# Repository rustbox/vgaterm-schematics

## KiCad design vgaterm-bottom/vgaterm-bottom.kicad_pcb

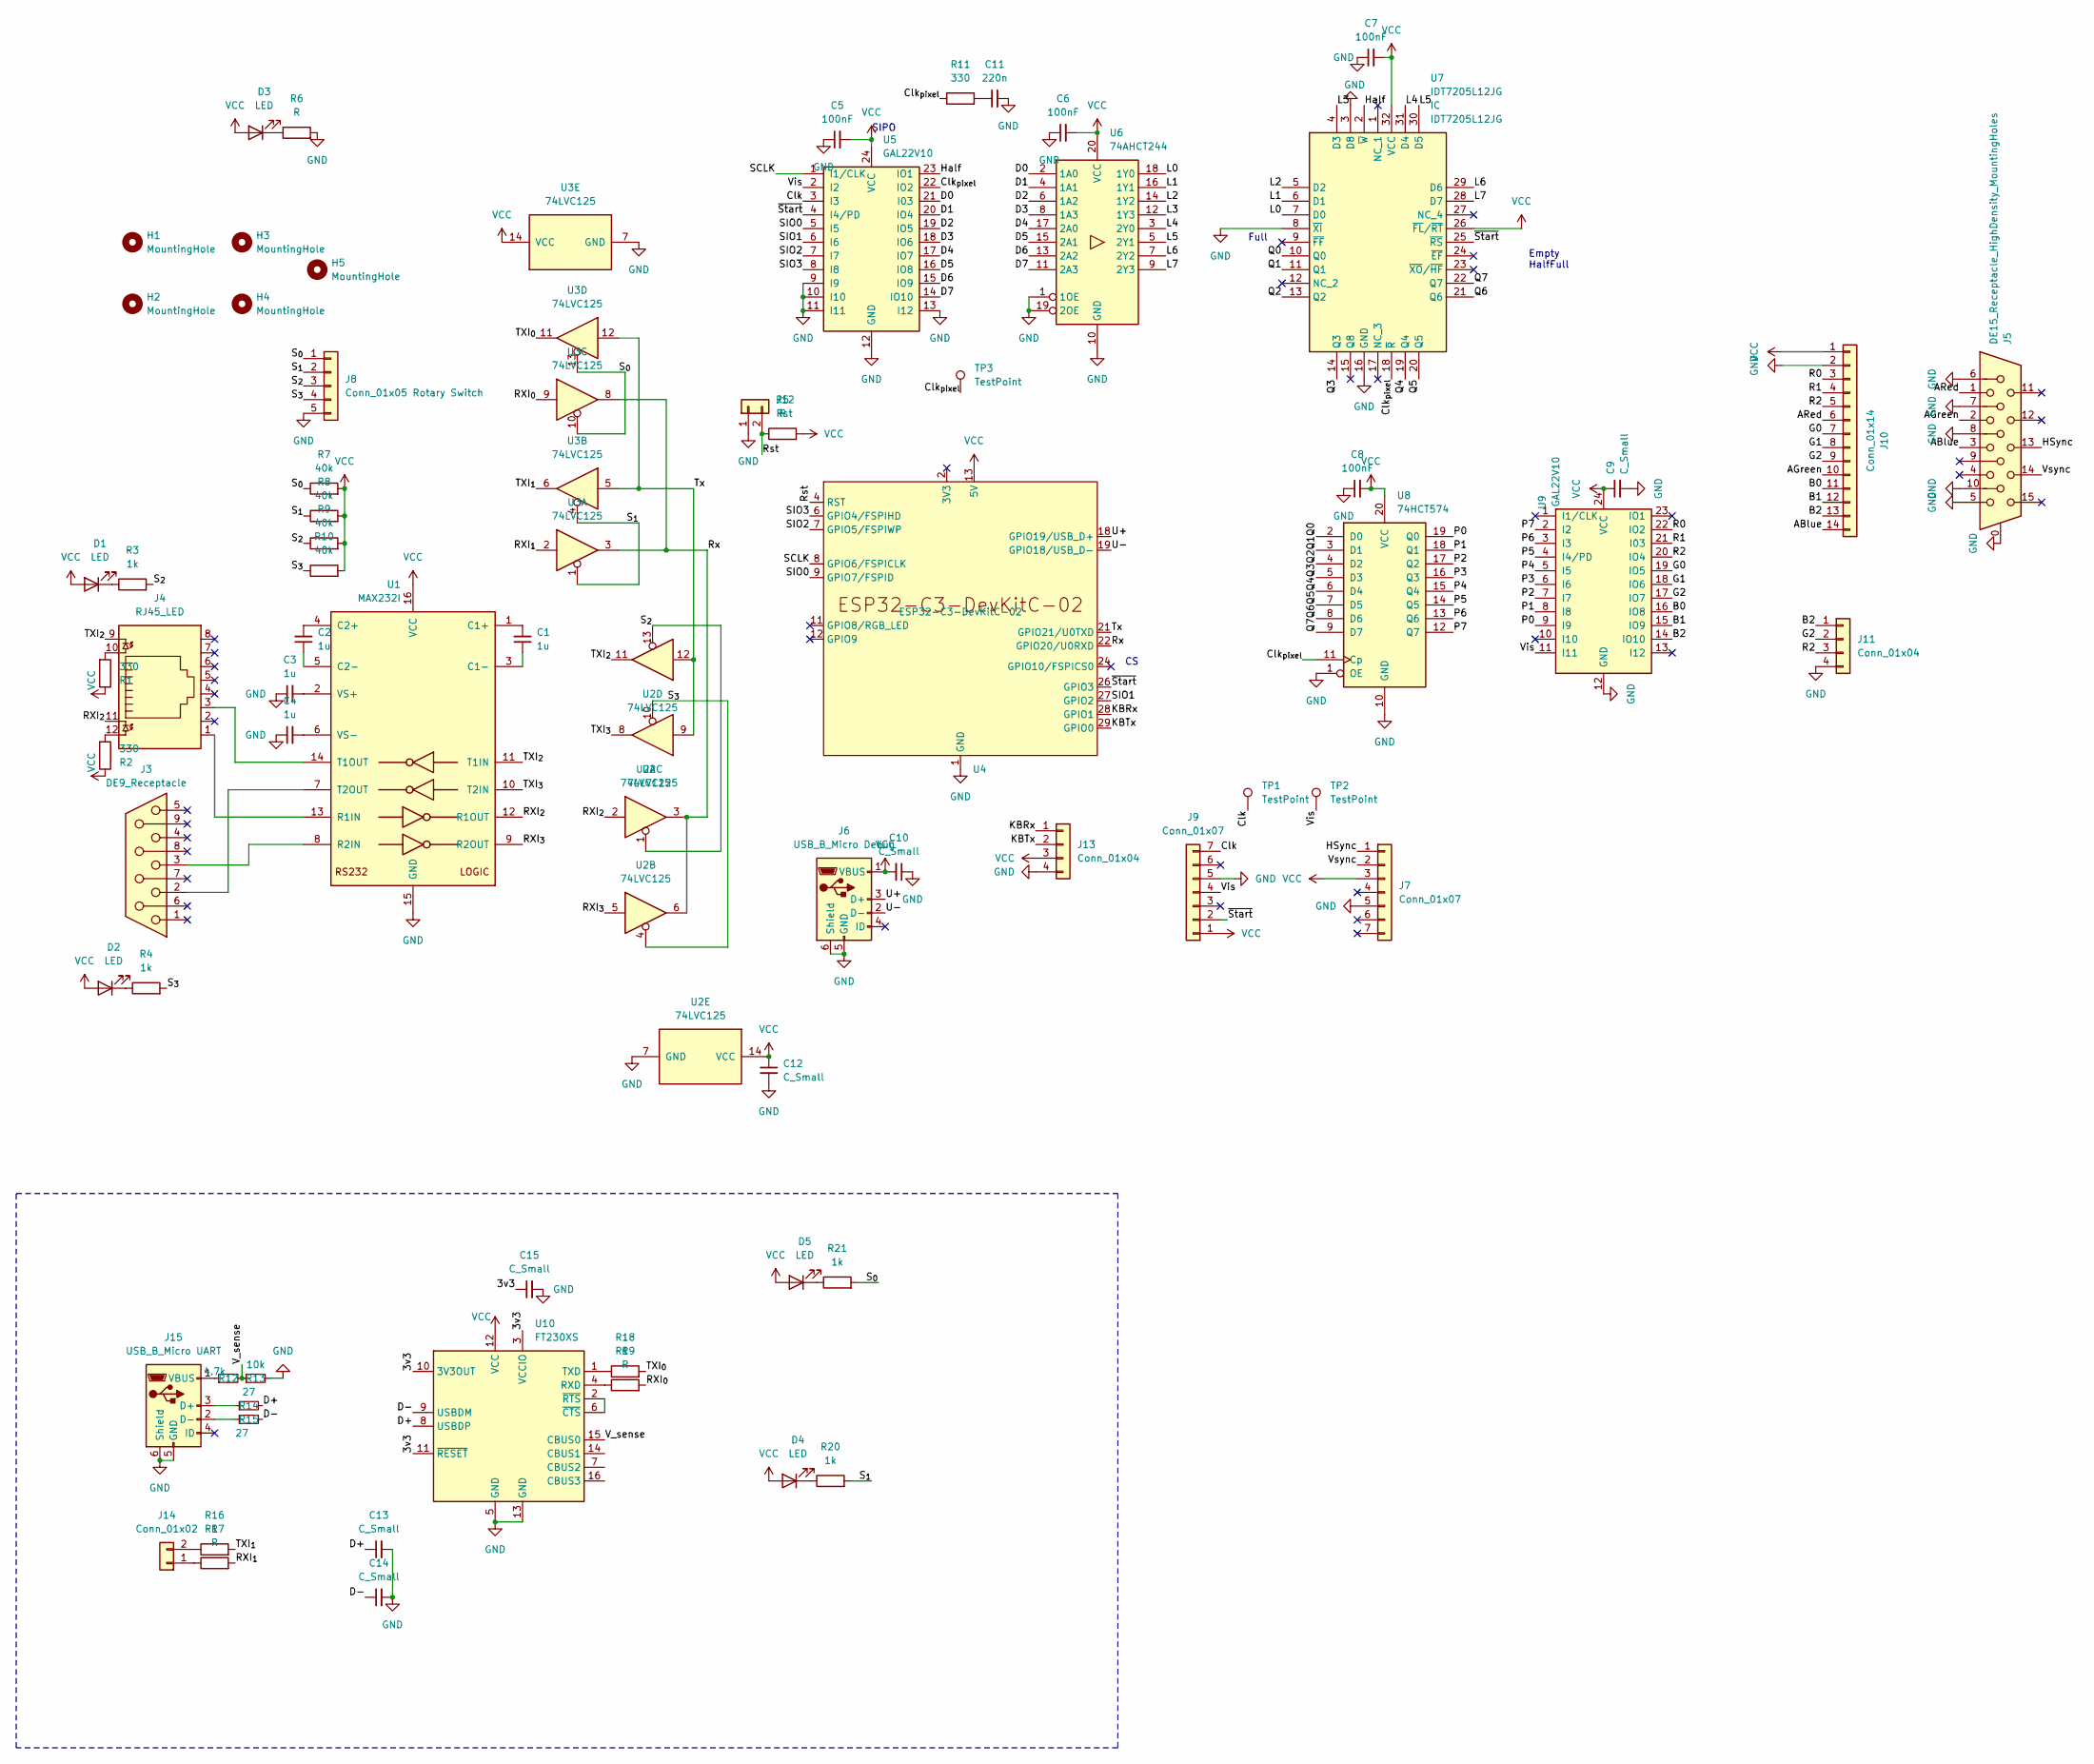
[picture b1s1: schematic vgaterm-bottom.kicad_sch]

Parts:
C1, C2, C3, C4: 1u; C_0805_2012Metric_Pad1.18x1.45mm_HandSolder
C5, C6, C7, C8: 100nF; C_0805_2012Metric_Pad1.18x1.45mm_HandSolder
C9, C10, C12, C13, C14, C15: C_Small; C_0805_2012Metric_Pad1.18x1.45mm_HandSolder
C11: 220n; C_0805_2012Metric_Pad1.18x1.45mm_HandSolder
D1, D2, D4, D5: LED; LED_D1.8mm_W1.8mm_H2.4mm_Horizontal_O1.27mm_Z1.6mm
D3: LED; LED_0805_2012Metric_Pad1.15x1.40mm_HandSolder
H1, H2, H3, H4, H5: MountingHole; MountingHole_2.2mm_M2_ISO7380
J3: DE9_Receptacle; DSUB-9_Female_Horizontal_P2.77x2.84mm_EdgePinOffset4.94mm_H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
J4: RJ45_LED; RJ45_Amphenol_RJHSE538X
J5: DE15_Receptacle_HighDensity_MountingHoles; DSUB-15-HD_Female_Horizontal_P2.29x2.54mm_EdgePinOffset8.35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
J6: USB_B_Micro Debug; USB_Micro-B_Molex-105017-0001
J7, J9: Conn_01x07; PinSocket_1x07_P2.54mm_Vertical
J8: Conn_01x05 Rotary Switch; PinHeader_1x05_P2.54mm_Vertical
J10: Conn_01x14; PinSocket_1x14_P2.54mm_Vertical
J11, J13: Conn_01x04; Molex_PicoBlade_53261-0471_1x04-1MP_P1.25mm_Horizontal
J12: Rst; PinHeader_1x02_P2.54mm_Vertical
J14: Conn_01x02; PinHeader_1x02_P2.54mm_Horizontal
J15: USB_B_Micro UART; USB_Micro-B_Molex-105017-0001
R1, R2, R11: 330; R_0805_2012Metric_Pad1.20x1.40mm_HandSolder
R3, R4, R20, R21: 1k; R_0805_2012Metric_Pad1.20x1.40mm_HandSolder
R5, R6, R16, R17, R18, R19: R; R_0805_2012Metric_Pad1.20x1.40mm_HandSolder
R7, R8, R9, R10: 40k; R_0805_2012Metric_Pad1.20x1.40mm_HandSolder
R12: 4.7k; R_0805_2012Metric_Pad1.20x1.40mm_HandSolder
R13: 10k; R_0805_2012Metric_Pad1.20x1.40mm_HandSolder
R14, R15: 27; R_0805_2012Metric_Pad1.20x1.40mm_HandSolder
TP1, TP2, TP3: TestPoint; TestPoint_THTPad_1.5x1.5mm_Drill0.7mm
U1: MAX232I; SOIC-16_3.9x9.9mm_P1.27mm
U2, U3: 74LVC125; TSSOP-14_4.4x5mm_P0.65mm
U4: ESP32-C3-DevKitC-02; espressif-2x15-devkit
U5, U9: GAL22V10; DIP-24_W7.62mm_Socket
U6: 74AHCT244; TSSOP-20_4.4x6.5mm_P0.65mm
U7: IDT7205L12JG; plcc32-socket; Manufacturer_Part_Number IDT7205L12JG
U8: 74HCT574; SOIC-20W_7.5x12.8mm_P1.27mm
U10: FT230XS; SSOP-16_3.9x4.9mm_P0.635mm

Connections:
3V3: U4.2 (3V3), U4.3 (3V3)
/3v3: C15.1, U10.3 (VCCIO), U10.10 (3V3OUT), U10.11 (~RESET)
/ABlue: J5.3, J10.14
/AGreen: J5.2, J10.10
/ARed: J5.1, J10.6
/B0: J10.11, U9.16 (IO8)
/B1: J10.12, U9.15 (IO9)
/B2: J10.13, J11.1, U9.14 (IO10)
/Clk: J9.7, TP1.1, U5.3 (I3)
/Clk_{pixel}: R11.1, TP3.1, U5.22 (IO2), U7.18 (~R), U8.11 (Cp)
/D0: U5.21 (I03), U6.2 (1A0)
/D1: U5.20 (IO4), U6.4 (1A1)
/D2: U5.19 (IO5), U6.6 (1A2)
/D3: U5.18 (IO6), U6.8 (1A3)
/D4: U5.17 (IO7), U6.17 (2A0)
/D5: U5.16 (IO8), U6.15 (2A1)
/D6: U5.15 (IO9), U6.13 (2A2)
/D7: U5.14 (IO10), U6.11 (2A3)
/D+: C13.1, R14.2, U10.8 (USBDP)
/D-: C14.1, R15.2, U10.9 (USBDM)
/G0: J10.7, U9.19 (IO5)
/G1: J10.8, U9.18 (IO6)
/G2: J10.9, J11.2, U9.17 (IO7)
/HSync: J5.13, J7.1
/Half: U5.23 (IO1), U7.2 (~W)
/KBRx: J13.1, U4.28 (GPIO1)
/KBTx: J13.2, U4.29 (GPIO0)
/L0: U6.18 (1Y0), U7.7 (D0)
/L1: U6.16 (1Y1), U7.6 (D1)
/L2: U6.14 (1Y2), U7.5 (D2)
/L3: U6.12 (1Y3), U7.4 (D3)
/L4: U6.3 (2Y0), U7.31 (D4)
/L5: U6.5 (2Y1), U7.30 (D5)
/L6: U6.7 (2Y2), U7.29 (D6)
/L7: U6.9 (2Y3), U7.28 (D7)
/P0: U8.19 (Q0), U9.9 (I9)
/P1: U8.18 (Q1), U9.8 (I8)
/P2: U8.17 (Q2), U9.7 (I7)
/P3: U8.16 (Q3), U9.6 (I6)
/P4: U8.15 (Q4), U9.5 (I5)
/P5: U8.14 (Q5), U9.4 (I4/PD)
/P6: U8.13 (Q6), U9.3 (I3)
/P7: U8.12 (Q7), U9.2 (I2)
/Q0: U7.10 (Q0), U8.2 (D0)
/Q1: U7.11 (Q1), U8.3 (D1)
/Q2: U7.13 (Q2), U8.4 (D2)
/Q3: U7.14 (Q3), U8.5 (D3)
/Q4: U7.19 (Q4), U8.6 (D4)
/Q5: U7.20 (Q5), U8.7 (D5)
/Q6: U7.21 (Q6), U8.8 (D6)
/Q7: U7.22 (Q7), U8.9 (D7)
/R0: J10.3, U9.22 (IO2)
/R1: J10.4, U9.21 (I03)
/R2: J10.5, J11.3, U9.20 (IO4)
/RXI_{0}: R19.2, U3.9
/RXI_{1}: R17.2, U3.2
/RXI_{2}: J4.11, U1.12 (R1OUT), U2.2
/RXI_{3}: U1.9 (R2OUT), U2.5
/Rst: J12.2, R5.1, U4.4 (RST)
/Rx: U2.3, U2.6, U3.3, U3.8, U4.22 (GPIO20/U0RXD)
/SCLK: U4.8 (GPIO6/FSPICLK), U5.1 (I1/CLK)
/SIO0: U4.9 (GPIO7/FSPID), U5.5 (I5)
/SIO1: U4.27 (GPIO2), U5.6 (I6)
/SIO2: U4.7 (GPIO5/FSPIWP), U5.7 (I7)
/SIO3: U4.6 (GPIO4/FSPIHD), U5.8 (I8)
/S_{0}: J8.1, R7.1, R21.2, U3.10, U3.13
/S_{1}: J8.2, R8.1, R20.2, U3.1, U3.4
/S_{2}: J8.3, R3.2, R9.1, U2.1, U2.13
/S_{3}: J8.4, R4.2, R10.1, U2.4, U2.10
/TXI_{0}: R18.2, U3.11
/TXI_{1}: R16.2, U3.6
/TXI_{2}: J4.9, U1.11 (T1IN), U2.11
/TXI_{3}: U1.10 (T2IN), U2.8
/Tx: U2.9, U2.12, U3.5, U3.12, U4.21 (GPIO21/U0TXD)
/U+: J6.3 (D+), U4.18 (GPIO19/USB_D+)
/U-: J6.2 (D-), U4.19 (GPIO18/USB_D-)
/V_sense: R12.2, R13.1, U10.15 (CBUS0)
/Vis: J9.4, TP2.1, U5.2 (I2), U9.11 (I11)
/Vsync: J5.14, J7.2
/~Start: J9.2, U4.26 (GPIO3), U5.4 (I4/PD), U7.25 (~RS)
GND: C3.1, C4.1, C5.1, C6.1, C7.1, C8.1, C9.2, C10.1, C11.2, C12.2, C13.2, C14.2, C15.2, J5.0, J5.5, J5.6, J5.7, J5.8, J5.10, J6.5 (GND), J6.6 (Shield), J7.5, J8.5, J9.5, J10.2, J11.4, J12.1, J13.4, J15.5 (GND), J15.6 (Shield), R6.2, R13.2, U1.15 (GND), U2.7 (GND), U3.7 (GND), U4.1 (GND), U4.5 (GND), U4.10 (GND), U4.15 (GND), U4.16 (GND), U4.17 (GND), U4.20 (GND), U4.23 (GND), U4.25 (GND), U4.30 (GND), U5.9 (I9), U5.10 (I10), U5.11 (I11), U5.12 (GND), U5.13 (I12), U6.1 (1OE), U6.10 (GND), U6.19 (2OE), U7.3 (D8), U7.8 (~XI), U7.16 (GND), U8.1 (OE), U8.10 (GND), U9.12 (GND), U10.5 (GND), U10.13 (GND)
unnamed: C11.1, R11.2
unnamed: D1.1 (K), R3.1
unnamed: D2.1 (K), R4.1
unnamed: D3.1 (K), R6.1
unnamed: D4.1 (K), R20.1
unnamed: D5.1 (K), R21.1
unnamed: J4.10, R1.2
unnamed: J4.12, R2.2
unnamed: J14.1, R17.1
unnamed: J14.2, R16.1
unnamed: J15.3 (D+), R14.1
unnamed: J15.2 (D-), R15.1
unnamed: J15.1 (VBUS), R12.1
unnamed: C1.2, U1.1 (C1+)
unnamed: C1.1, U1.3 (C1-)
unnamed: C2.2, U1.4 (C2+)
unnamed: C2.1, U1.5 (C2-)
unnamed: J4.1, U1.13 (R1IN)
unnamed: J3.3, U1.8 (R2IN)
unnamed: J4.3, U1.14 (T1OUT)
unnamed: J3.2, U1.7 (T2OUT)
unnamed: C3.2, U1.2 (VS+)
unnamed: C4.2, U1.6 (VS-)
unnamed: R19.1, U10.4 (RXD)
unnamed: R18.1, U10.1 (TXD)
unnamed: U10.2 (~RTS), U10.6 (~CTS)
VCC: C5.2, C6.2, C7.2, C8.2, C9.1, C10.2, C12.1, D1.2 (A), D2.2 (A), D3.2 (A), D4.2 (A), D5.2 (A), J6.1 (VBUS), J7.3, J9.1, J10.1, J13.3, R1.1, R2.1, R5.2, R7.2, R8.2, R9.2, R10.2, U1.16 (VCC), U2.14 (VCC), U3.14 (VCC), U4.13 (5V), U4.14 (5V), U5.24 (VCC), U6.20 (VCC), U7.26 (~FL/~RT), U7.32 (VCC), U8.20 (VCC), U9.24 (VCC), U10.12 (VCC)

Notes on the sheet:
Empty HalfFull
SIPO
Full

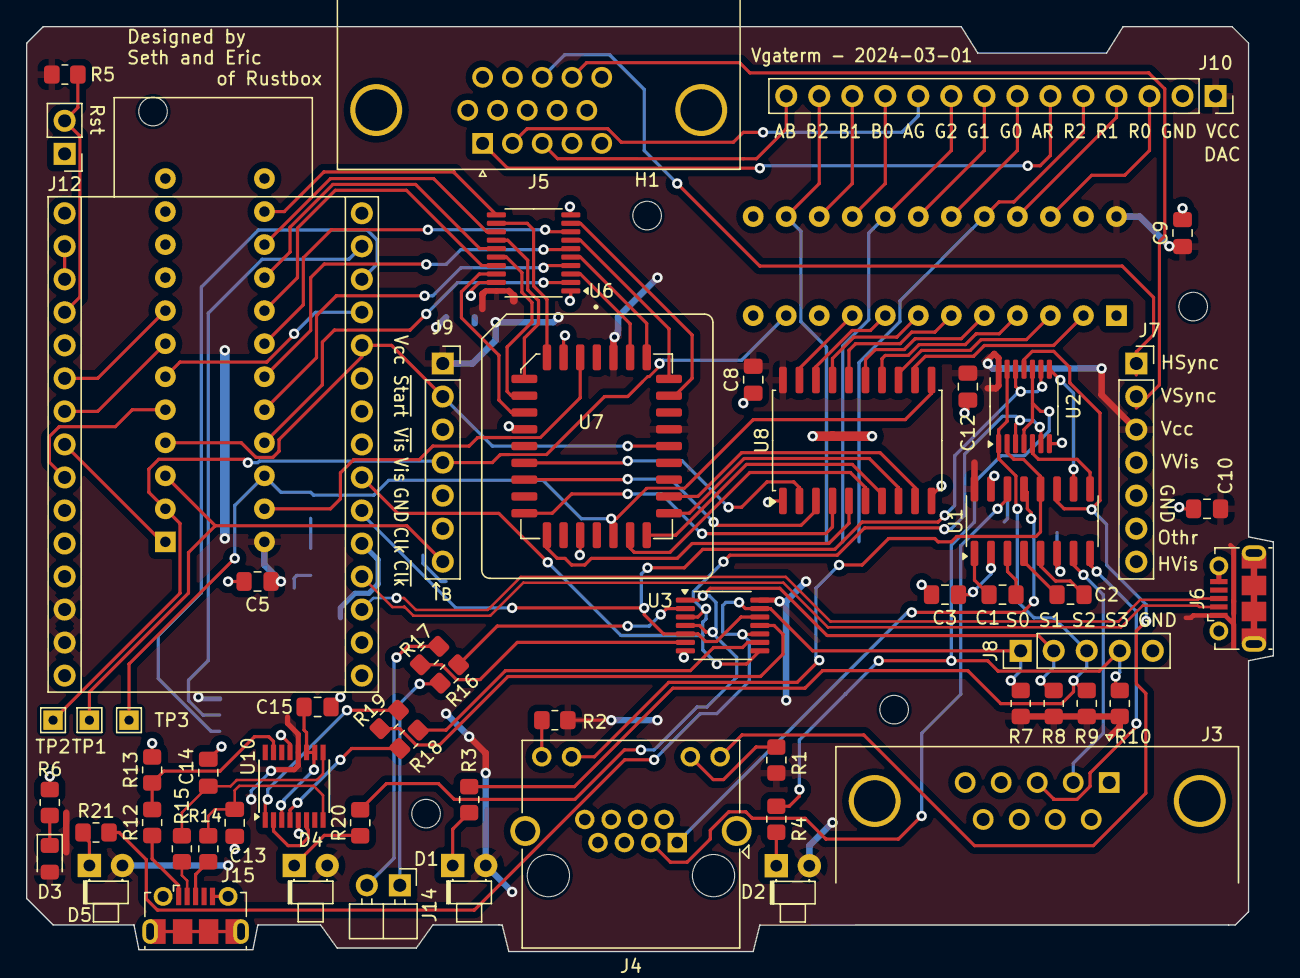
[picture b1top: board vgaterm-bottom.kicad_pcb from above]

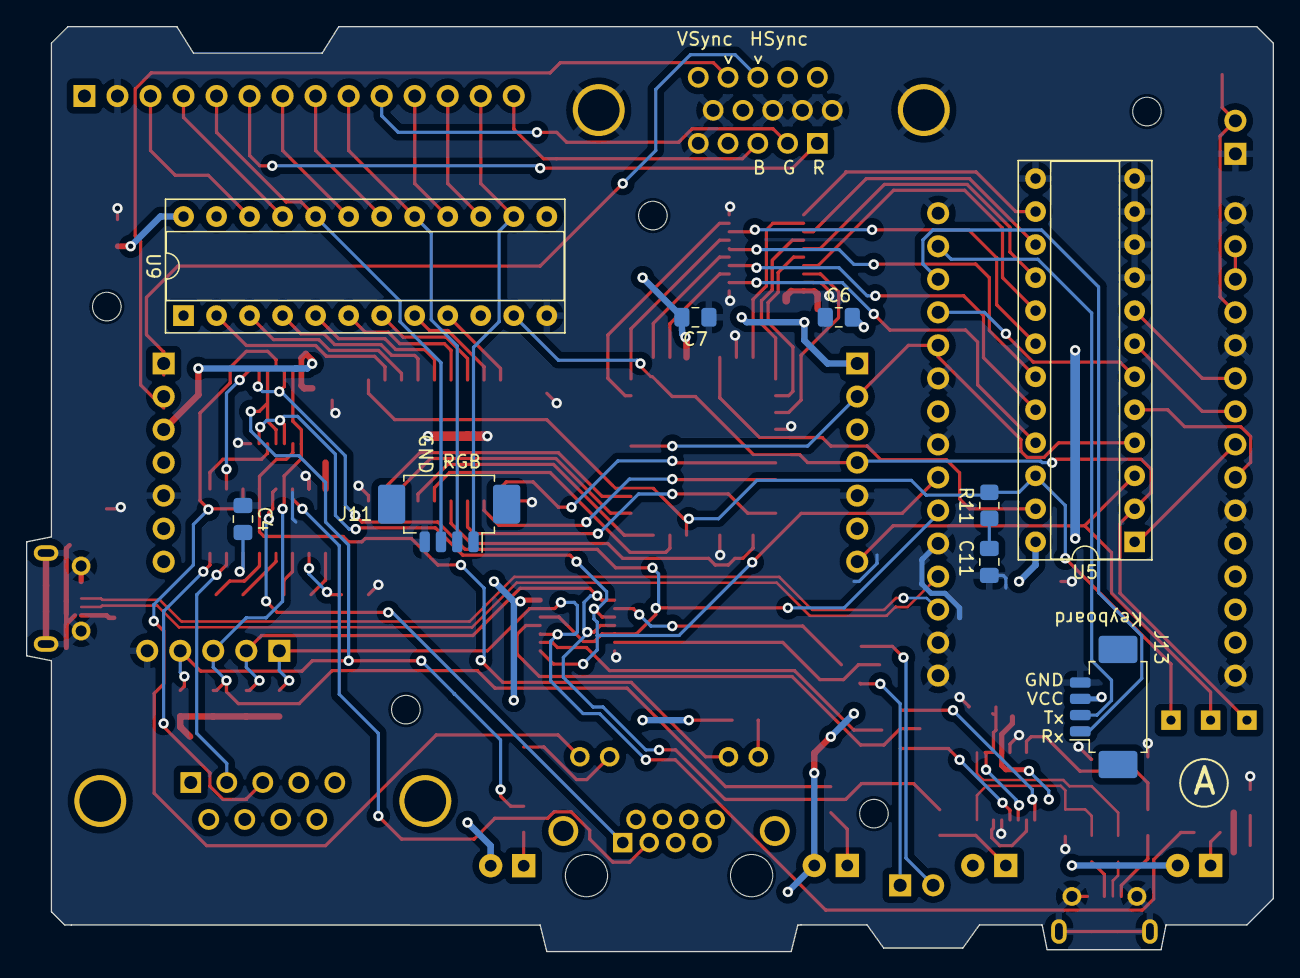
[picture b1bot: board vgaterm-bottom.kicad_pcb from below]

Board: 2 copper layers, 95.9 x 71.1 mm, 72 parts (9 on the bottom side), 108 nets.

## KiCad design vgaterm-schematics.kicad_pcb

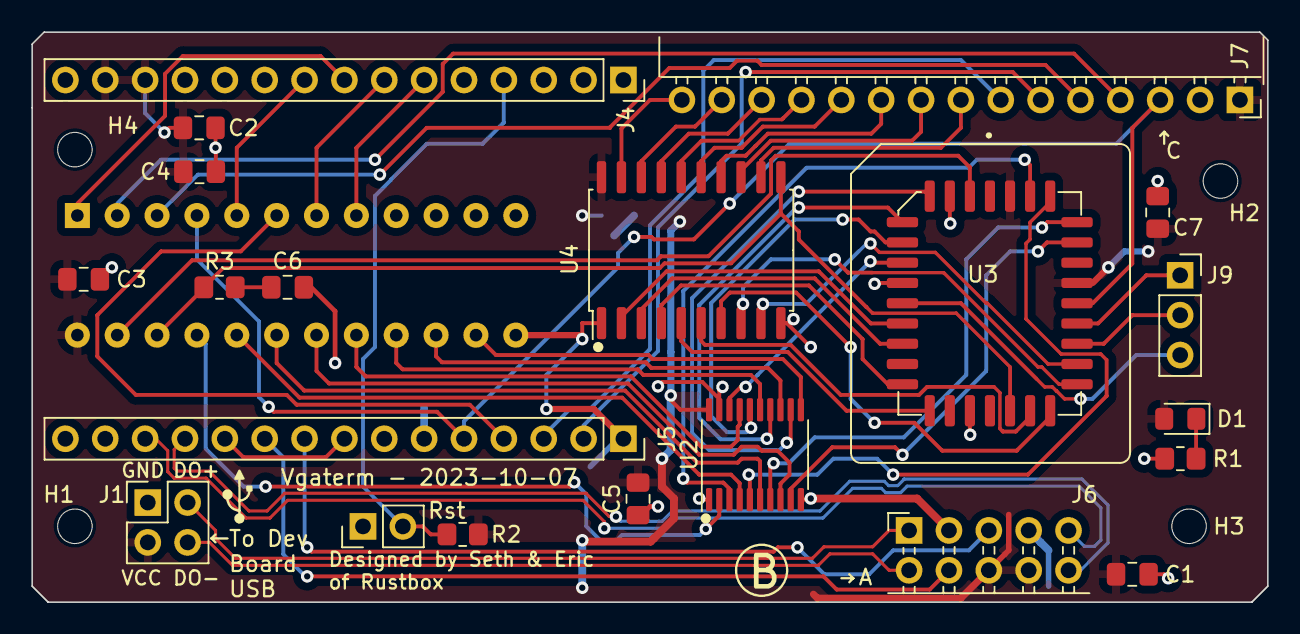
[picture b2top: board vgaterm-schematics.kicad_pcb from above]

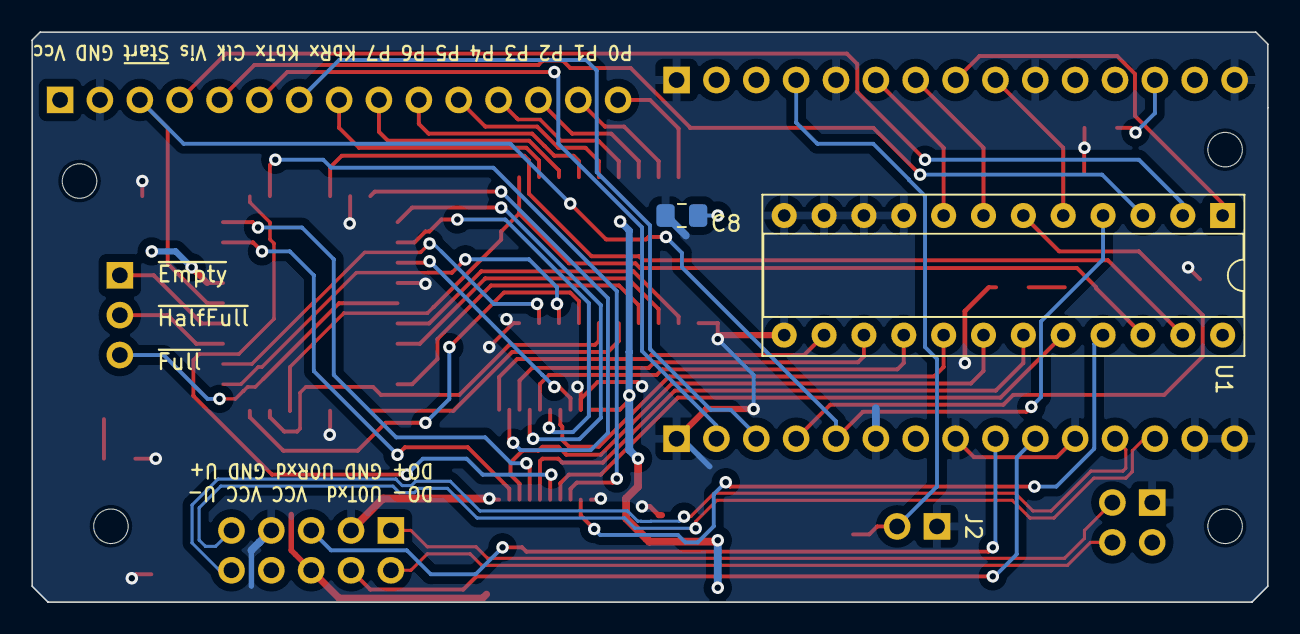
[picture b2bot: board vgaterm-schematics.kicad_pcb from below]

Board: 2 copper layers, 78.7 x 36.3 mm, 27 parts (2 on the bottom side), 58 nets.

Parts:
C1, C2, C4: 10uF; C_0805_2012Metric_Pad1.18x1.45mm_HandSolder
C3, C5, C7, C8: 100nF; C_0805_2012Metric_Pad1.18x1.45mm_HandSolder
C6: 220n; C_0805_2012Metric_Pad1.18x1.45mm_HandSolder
D1: LED; LED_0805_2012Metric_Pad1.15x1.40mm_HandSolder
H1, H2, H3, H4: MountingHole; MountingHole_2.2mm_M2
J1: Conn_01x04; PinHeader_2x02_P2.54mm_Vertical
J2: Rst; PinHeader_1x02_P2.54mm_Vertical
J4, J5: Conn_01x15_Socket; PinSocket_1x15_P2.54mm_Vertical
J6: Conn_01x10; PinSocket_2x05_P2.54mm_Horizontal
J7: Conn_01x15; PinSocket_1x15_P2.54mm_Horizontal
J9: Conn_01x03_Socket; PinSocket_1x03_P2.54mm_Vertical
R1, R2: R; R_0805_2012Metric_Pad1.20x1.40mm_HandSolder
R3: 330; R_0805_2012Metric_Pad1.20x1.40mm_HandSolder
U1: GAL22V10; DIP-24_W7.62mm_Socket
U2: 74AHCT244; TSSOP-20_4.4x6.5mm_P0.65mm
U3: IDT7205L12JG; plcc32-socket
U4: 74HCT574; SOIC-20W_7.5x12.8mm_P1.27mm

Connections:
/Clk: J7.5, U1.3 (I3)
/Clk_{pixel}: R3.1, U1.22 (IO2), U3.18 (~R), U4.11 (Cp)
/D0: U1.21 (I03), U2.2 (1A0)
/D1: U1.20 (IO4), U2.4 (1A1)
/D2: U1.19 (IO5), U2.6 (1A2)
/D3: U1.18 (IO6), U2.8 (1A3)
/D4: U1.17 (IO7), U2.17 (2A0)
/D5: U1.16 (IO8), U2.15 (2A1)
/D6: U1.15 (IO9), U2.13 (2A2)
/D7: U1.14 (IO10), U2.11 (2A3)
/DO+: J1.2, J6.1
/DO-: J1.4, J6.2
/Empty: J9.1, U3.24 (~EF)
/Full: J9.3, U3.9 (~FF)
/Half: U1.23 (IO1), U3.2 (~W)
/HalfFull: J9.2, U3.23 (~XO/~HF)
/KB_{Rx}: J5.3, J7.7
/KB_{Tx}: J5.2, J7.6
/L0: U2.18 (1Y0), U3.7 (D0)
/L1: U2.16 (1Y1), U3.6 (D1)
/L2: U2.14 (1Y2), U3.5 (D2)
/L3: U2.12 (1Y3), U3.4 (D3)
/L4: U2.3 (2Y0), U3.31 (D4)
/L5: U2.5 (2Y1), U3.30 (D5)
/L6: U2.7 (2Y2), U3.29 (D6)
/L7: U2.9 (2Y3), U3.28 (D7)
/P0: J7.15, U4.19 (Q0)
/P1: J7.14, U4.18 (Q1)
/P2: J7.13, U4.17 (Q2)
/P3: J7.12, U4.16 (Q3)
/P4: J7.11, U4.15 (Q4)
/P5: J7.10, U4.14 (Q5)
/P6: J7.9, U4.13 (Q6)
/P7: J7.8, U4.12 (Q7)
/Q0: U3.10 (Q0), U4.2 (D0)
/Q1: U3.11 (Q1), U4.3 (D1)
/Q2: U3.13 (Q2), U4.4 (D2)
/Q3: U3.14 (Q3), U4.5 (D3)
/Q4: U3.19 (Q4), U4.6 (D4)
/Q5: U3.20 (Q5), U4.7 (D5)
/Q6: U3.21 (Q6), U4.8 (D6)
/Q7: U3.22 (Q7), U4.9 (D7)
/Rst: J2.2, J4.4, R2.1
/SCLK: J4.8, U1.1 (I1/CLK)
/SIO0: J4.9, U1.5 (I5)
/SIO1: J5.4, U1.6 (I6)
/SIO2: J4.7, U1.7 (I7)
/SIO3: J4.6, U1.8 (I8)
/U0Rxd: J5.9, J6.5
/U0Txd: J5.10, J6.4
/U+: J5.13, J6.9
/U-: J5.12, J6.10
/Vis: J7.4, U1.2 (I2)
/~StartFrame: J5.5, J7.3, U1.4 (I4/PD), U3.25 (~RS)
GND: C1.1, C2.1, C3.1, C4.1, C5.1, C6.2, C7.1, C8.1, J1.1, J2.1, J4.1, J4.5, J4.10, J4.15, J5.1, J5.6, J5.8, J5.11, J5.14, J5.15, J6.3, J6.7, J7.2, R1.2, U1.9 (I9), U1.10 (I10), U1.11 (I11), U1.12 (GND), U1.13 (I12), U2.1 (1OE), U2.10 (GND), U2.19 (2OE), U3.3 (D8), U3.8 (~XI), U3.16 (GND), U4.1 (OE), U4.10 (GND)
unnamed: C6.1, R3.2
unnamed: D1.1 (K), R1.1
VCC: C1.2, C2.2, C3.2, C4.2, C5.2, C7.2, C8.2, D1.2 (A), J1.3, J4.13, J4.14, J6.6, J6.8, J7.1, R2.2, U1.24 (VCC), U2.20 (VCC), U3.26 (~FL/~RT), U3.32 (VCC), U4.20 (VCC)

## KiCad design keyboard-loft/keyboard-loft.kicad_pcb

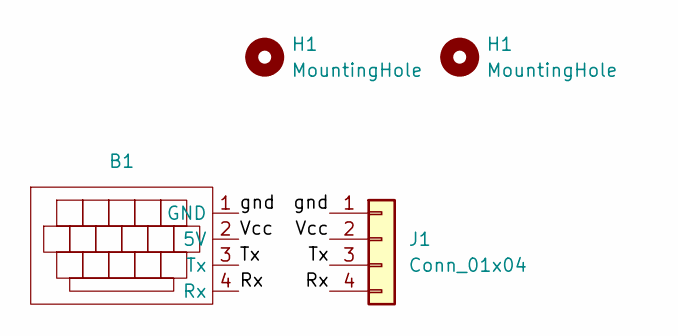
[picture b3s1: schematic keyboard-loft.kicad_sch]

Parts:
B1: USB-UART-board
H1: MountingHole; MountingHole_2.2mm_M2_ISO7380
J1: Conn_01x04; PinHeader_1x04_P2.54mm_Horizontal

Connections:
/Rx: B1.4 (Rx), J1.4
/Tx: B1.3 (Tx), J1.3
/Vcc: B1.2 (5V), J1.2
/gnd: B1.1 (GND), J1.1

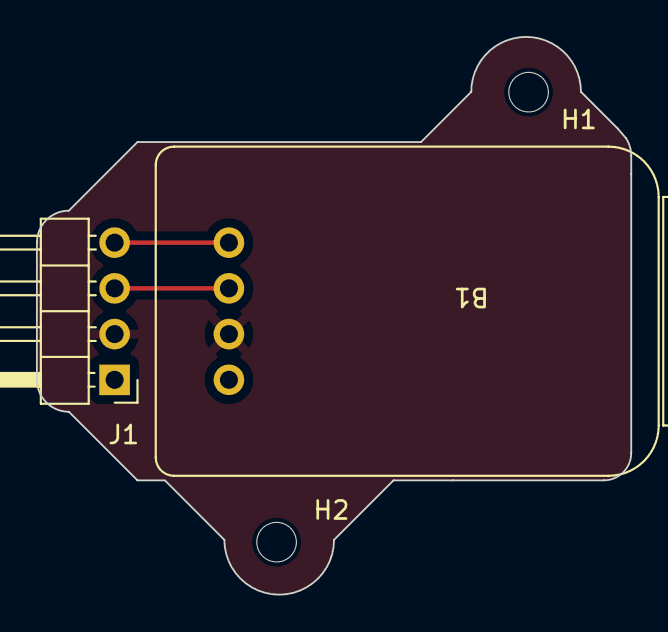
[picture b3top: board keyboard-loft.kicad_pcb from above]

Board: 2 copper layers, 33.0 x 31.0 mm, 4 parts (0 on the bottom side), 4 nets.

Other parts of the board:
H2: MountingHole; MountingHole_2.2mm_M2_ISO7380

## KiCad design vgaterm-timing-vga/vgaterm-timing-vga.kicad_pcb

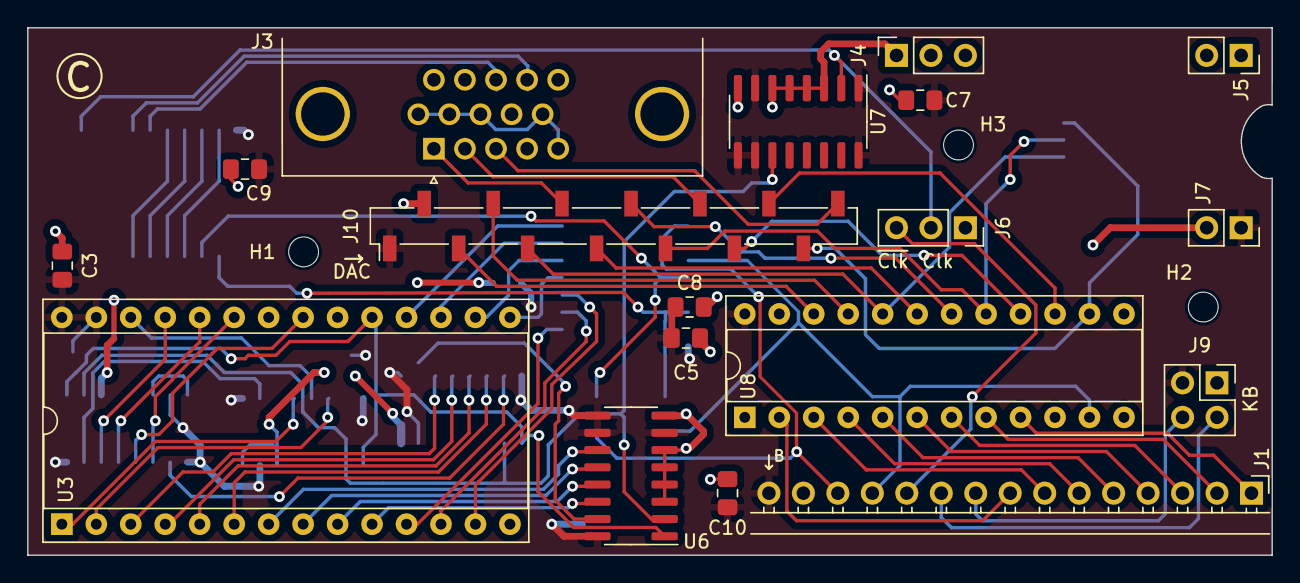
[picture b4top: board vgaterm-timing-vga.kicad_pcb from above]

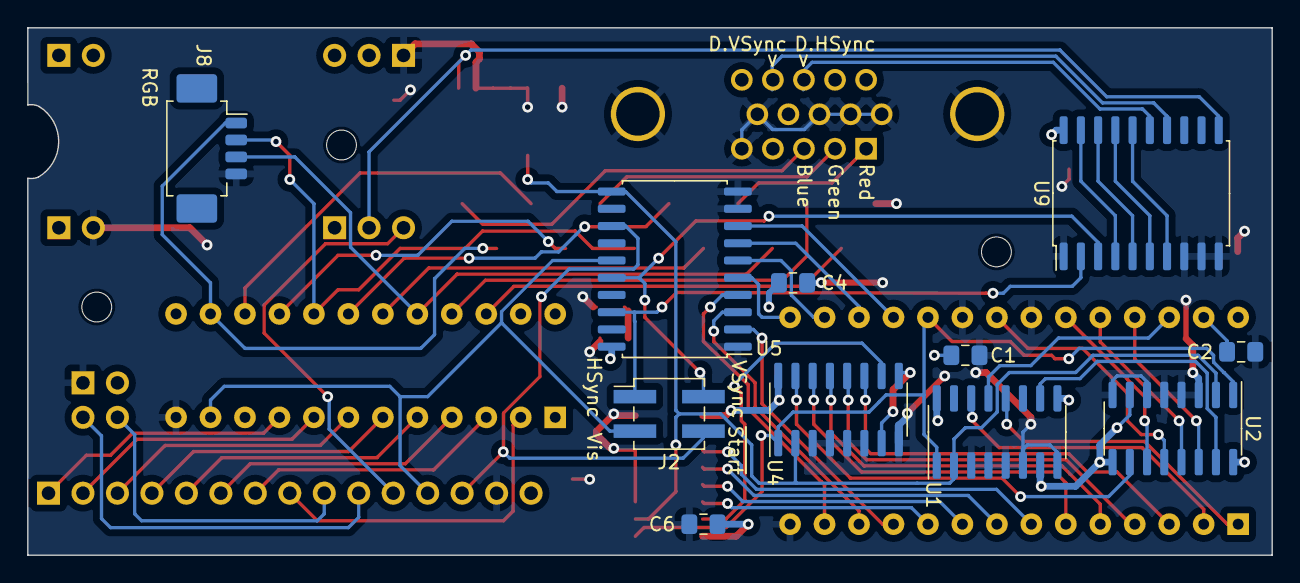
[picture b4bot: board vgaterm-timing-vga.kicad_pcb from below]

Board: 2 copper layers, 91.7 x 38.9 mm, 32 parts (11 on the bottom side), 63 nets.

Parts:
C1, C2, C3, C4, C5, C6, C7, C8, C9: C_Small; C_0805_2012Metric_Pad1.18x1.45mm_HandSolder
C10: 10uF; C_0805_2012Metric_Pad1.18x1.45mm_HandSolder
H1, H2, H3: MountingHole; MountingHole_2.2mm_M2_ISO7380
J1: Conn_01x15; PinHeader_1x15_P2.54mm_Horizontal
J2: Conn_01x04; PinHeader_2x02_P2.54mm_Vertical_SMD
J3: DE15_Receptacle_HighDensity_MountingHoles; DSUB-15-HD_Female_Horizontal_P2.29x2.54mm_EdgePinOffset8.35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
J4, J6: Conn_01x03_Pin; PinSocket_1x03_P2.54mm_Vertical
J5, J7: Conn_01x02_Pin; PinSocket_1x02_P2.54mm_Vertical
J8: Conn_01x04; Molex_PicoBlade_53261-0471_1x04-1MP_P1.25mm_Horizontal
J9: Conn_01x04; PinSocket_2x02_P2.54mm_Vertical
J10: Conn_01x14; PinSocket_1x14_P2.54mm_Vertical_SMD_Pin1Left
U1, U2, U4, U6, U7: 74LS161; SOIC-16_3.9x9.9mm_P1.27mm
U3: 28C256; DIP-28_W15.24mm_Socket
U5, U9: 74HCT574; SOIC-20W_7.5x12.8mm_P1.27mm
U8: GAL22V10; DIP-24_W7.62mm_Socket

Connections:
/A0: U3.10 (A0), U6.14 (Q0)
/A1: U3.9 (A1), U6.13 (Q1)
/A2: U3.8 (A2), U6.12 (Q2)
/A3: U3.7 (A3), U6.11 (Q3)
/A4: U3.6 (A4), U4.14 (Q0)
/A5: U3.5 (A5), U4.13 (Q1)
/A6: U3.4 (A6), U4.12 (Q2)
/A7: U3.3 (A7), U4.11 (Q3)
/A8: U2.14 (Q0), U3.25 (A8)
/A9: U2.13 (Q1), U3.24 (A9)
/A10: U2.12 (Q2), U3.21 (A10)
/A11: U2.11 (Q3), U3.23 (A11)
/A12: U1.14 (Q0), U3.2 (A12)
/A13: U1.13 (Q1), U3.26 (A13)
/A14: U1.12 (Q2), U3.1 (A14)
/ABlue: J3.3, J10.14
/AGreen: J3.2, J10.10
/ARed: J3.1, J10.6
/A_{out}: J6.2, U7.2 (CP), U9.11 (Cp)
/B0: J10.11, U8.16 (IO8)
/B1: J10.12, U8.15 (IO9)
/B2: J8.1, J10.13, U8.14 (IO10)
/CLK_{sync}: U1.2 (CP), U2.2 (CP), U4.2 (CP), U5.11 (Cp), U6.2 (CP), U7.11 (Q3)
/G0: J10.7, U8.19 (IO5)
/G1: J10.8, U8.18 (IO6)
/G2: J8.2, J10.9, U8.17 (IO7)
/HSYNC_{1}: U9.4 (D2), U9.19 (Q0)
/HSYNC_{2}: U9.6 (D4), U9.17 (Q2)
/HSYNC_{3}: J3.13, U9.15 (Q4)
/HSync: J2.1, U5.18 (Q1), U9.2 (D0)
/KBRx: J1.9, J9.4
/KBTx: J1.10, J9.3
/P0: J1.1, U8.9 (I9)
/P1: J1.2, U8.8 (I8)
/P2: J1.3, U8.7 (I7)
/P3: J1.4, U8.6 (I6)
/P4: J1.5, U8.5 (I5)
/P5: J1.6, U8.4 (I4/PD)
/P6: J1.7, U8.3 (I3)
/P7: J1.8, U8.2 (I2)
/R0: J10.3, U8.22 (IO2)
/R1: J10.4, U8.21 (I03)
/R2: J8.3, J10.5, U8.20 (IO4)
/VSYNC_{1}: U9.5 (D3), U9.18 (Q1)
/VSYNC_{2}: U9.7 (D5), U9.16 (Q3)
/VSYNC_{3}: J3.14, U9.14 (Q5)
/Vis: J1.12, J2.3, U5.15 (Q4), U8.11 (I11)
/Vsync: J2.2, U5.16 (Q3), U9.3 (D1)
/~A_{out}: J1.11, J6.3
/~RESET: U1.1 (~MR), U2.1 (~MR), U3.19 (D7), U4.1 (~MR), U6.1 (~MR)
/~StartFrame: J1.13, J2.4, U5.13 (Q6)
GND: C1.2, C2.2, C3.2, C4.2, C5.2, C6.2, C7.2, C8.2, C9.2, C10.1, J1.14, J3.0, J3.5, J3.6, J3.7, J3.8, J3.10, J4.1, J7.2, J8.4, J9.1, J10.2, U1.3 (D0), U1.4 (D1), U1.5 (D2), U1.6 (D3), U1.8 (GND), U2.3 (D0), U2.4 (D1), U2.5 (D2), U2.6 (D3), U2.8 (GND), U3.14 (GND), U3.20 (~CS), U3.22 (~OE), U4.3 (D0), U4.4 (D1), U4.5 (D2), U4.6 (D3), U4.8 (GND), U5.1 (OE), U5.9 (D7), U5.10 (GND), U6.3 (D0), U6.4 (D1), U6.5 (D2), U6.6 (D3), U6.8 (GND), U7.3 (D0), U7.4 (D1), U7.5 (D2), U7.6 (D3), U7.8 (GND), U8.12 (GND), U9.1 (OE), U9.8 (D6), U9.9 (D7), U9.10 (GND)
unnamed: U1.10 (CET), U2.15 (TC)
unnamed: U2.10 (CET), U4.15 (TC)
unnamed: U3.11 (D0), U5.2 (D0)
unnamed: U3.12 (D1), U5.3 (D1)
unnamed: U3.13 (D2), U5.4 (D2)
unnamed: U3.15 (D3), U5.5 (D3)
unnamed: U3.16 (D4), U5.6 (D4)
unnamed: U3.17 (D5), U5.7 (D5)
unnamed: U3.18 (D6), U5.8 (D6)
unnamed: U4.10 (CET), U6.15 (TC)
VCC: C1.1, C2.1, C3.1, C4.1, C5.1, C6.1, C7.1, C8.1, C9.1, C10.2, J1.15, J7.1, J9.2, J10.1, U1.7 (CEP), U1.9 (~PE), U1.16 (VCC), U2.7 (CEP), U2.9 (~PE), U2.16 (VCC), U3.27 (~WE), U3.28 (VCC), U4.7 (CEP), U4.9 (~PE), U4.16 (VCC), U5.20 (VCC), U6.7 (CEP), U6.9 (~PE), U6.10 (CET), U6.16 (VCC), U7.1 (~MR), U7.7 (CEP), U7.9 (~PE), U7.10 (CET), U7.16 (VCC), U8.24 (VCC), U9.20 (VCC)

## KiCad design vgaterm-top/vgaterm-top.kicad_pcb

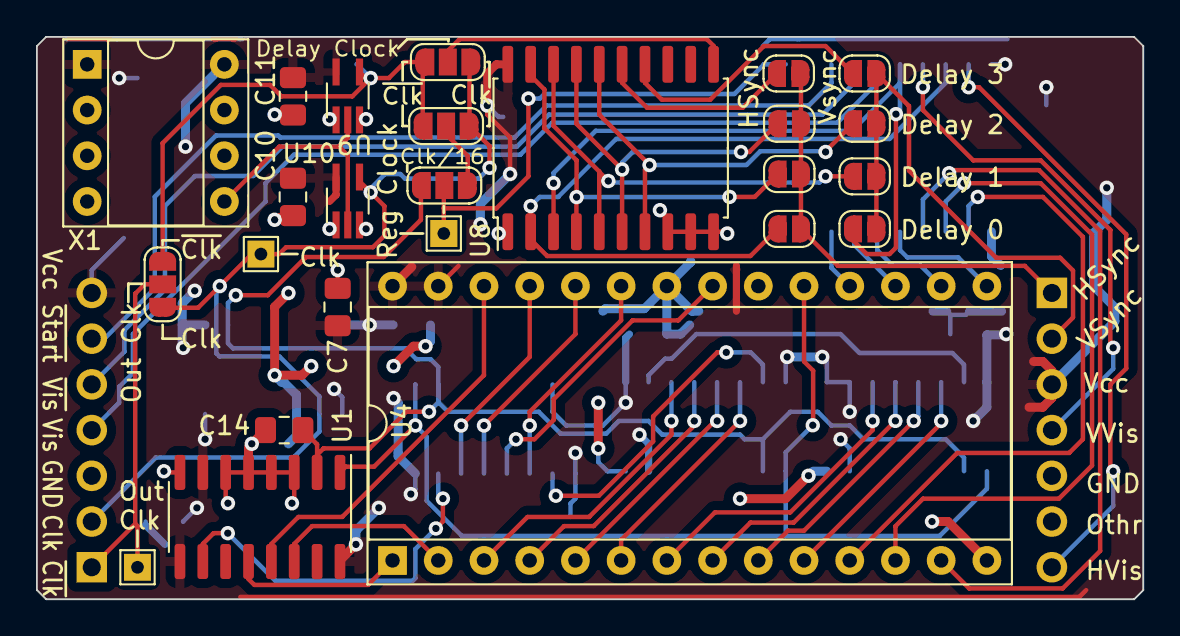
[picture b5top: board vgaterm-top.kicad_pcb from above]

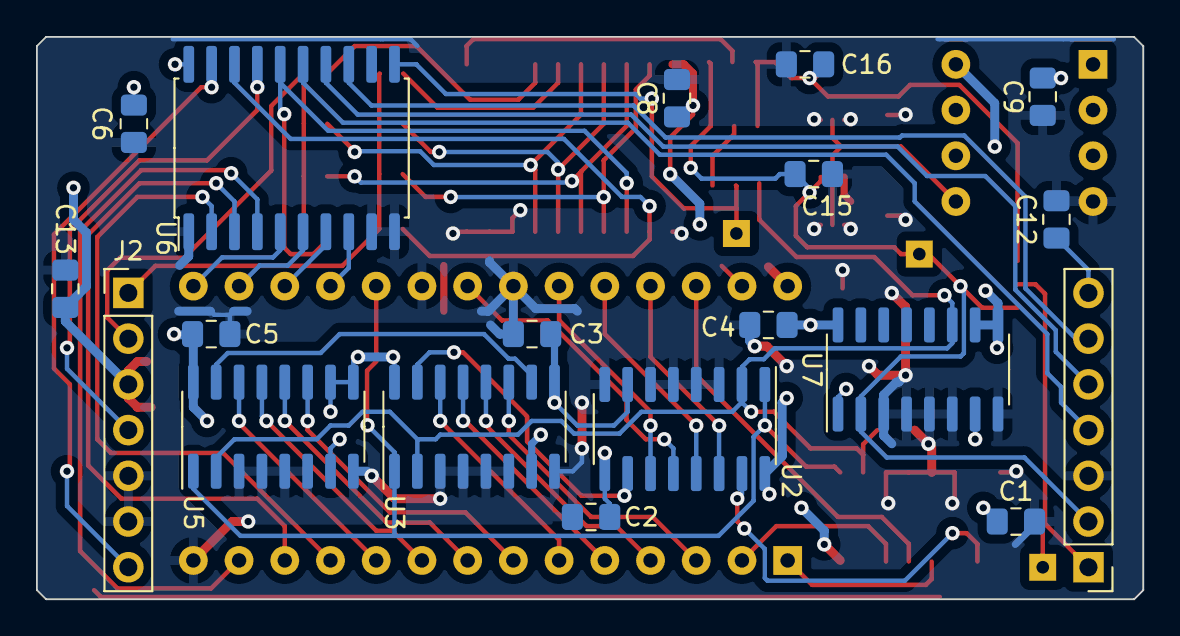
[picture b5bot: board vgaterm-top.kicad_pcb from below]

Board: 2 copper layers, 61.5 x 31.2 mm, 44 parts (19 on the bottom side), 51 nets.

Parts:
C1, C2, C3, C4, C5, C6, C7, C8, C14, C15, C16: C_Small; C_0805_2012Metric_Pad1.18x1.45mm_HandSolder
C9, C10, C11: 100n; C_0805_2012Metric_Pad1.18x1.45mm_HandSolder
C12, C13: 10u; C_0805_2012Metric_Pad1.18x1.45mm_HandSolder
J1, J2: Conn_01x07; PinHeader_1x07_P2.54mm_Vertical
JP1, JP3, JP11, JP12: SolderJumper_3_Open; SolderJumper-3_P1.3mm_Open_RoundedPad1.0x1.5mm_NumberLabels
JP2, JP4, JP5, JP6, JP7, JP8, JP9, JP10: SolderJumper_2_Open; SolderJumper-2_P1.3mm_Open_RoundedPad1.0x1.5mm
TP1, TP2, TP3: TestPoint; TestPoint_THTPad_1.5x1.5mm_Drill0.7mm
U1, U2, U3, U5, U7: 74LS161; SOIC-16_3.9x9.9mm_P1.27mm
U4: 28C256; DIP-28_W15.24mm_Socket
U6, U8: 74HCT574; SOIC-20W_7.5x12.8mm_P1.27mm
U9: 74AUC1G240; SOT-353_SC-70-5_Handsoldering
U10: 74AHC1G125; SOT-353_SC-70-5_Handsoldering
X1: CXO_DIP8; DIP-8_W7.62mm_Socket

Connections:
/A0: U4.10 (A0), U5.14 (Q0)
/A1: U4.9 (A1), U5.13 (Q1)
/A2: U4.8 (A2), U5.12 (Q2)
/A3: U4.7 (A3), U5.11 (Q3)
/A4: U3.14 (Q0), U4.6 (A4)
/A5: U3.13 (Q1), U4.5 (A5)
/A6: U3.12 (Q2), U4.4 (A6)
/A7: U3.11 (Q3), U4.3 (A7)
/A8: U2.14 (Q0), U4.25 (A8)
/A9: U2.13 (Q1), U4.24 (A9)
/A10: U2.12 (Q2), U4.21 (A10)
/A11: U2.11 (Q3), U4.23 (A11)
/A12: U1.14 (Q0), U4.2 (A12)
/A13: U1.13 (Q1), U4.26 (A13)
/A14: U1.12 (Q2), U4.1 (A14)
/CLK_{sync}: C14.1, JP3.1 (A), U1.2 (CP), U2.2 (CP), U3.2 (CP), U5.2 (CP), U7.11 (Q3)
/Clk: C15.1, J1.2, JP1.1 (A), JP11.3 (B), JP12.1 (A), TP2.1, U7.2 (CP), U10.4
/HSYNC_{1}: JP5.1 (A), U8.4 (D2), U8.19 (Q0)
/HSYNC_{2}: JP7.1 (A), U8.6 (D4), U8.17 (Q2)
/HSYNC_{3}: JP9.1 (A), U8.15 (Q4)
/HSYNC_{sel}: J2.1, JP2.2 (B), JP5.2 (B), JP7.2 (B), JP9.2 (B)
/HSync: JP2.1 (A), U6.18 (Q1), U8.2 (D0)
/HVis: J2.7, U6.19 (Q0)
/VSYNC_{1}: JP6.1 (A), U8.5 (D3), U8.18 (Q1)
/VSYNC_{2}: JP8.1 (A), U8.7 (D5), U8.16 (Q3)
/VSYNC_{3}: JP10.1 (A), U8.14 (Q5)
/VSYNC_{sel}: J2.2, JP4.2 (B), JP6.2 (B), JP8.2 (B), JP10.2 (B)
/VertVis: J2.4, U6.17 (Q2)
/Vis: J1.4, U6.15 (Q4)
/Vsync: JP4.1 (A), U6.16 (Q3), U8.3 (D1)
/~Clk: C16.1, JP1.3 (B), JP11.1 (A), JP12.3 (B), U9.4
/~RESET: U1.1 (~MR), U2.1 (~MR), U3.1 (~MR), U4.19 (D7), U5.1 (~MR)
/~StartFrame: J1.6, U6.13 (Q6)
/~Vis: J1.5, U6.14 (Q5)
GND: C1.2, C2.2, C3.2, C4.2, C5.2, C6.2, C7.2, C8.2, C9.2, C10.1, C11.1, C12.2, C13.2, C14.2, C15.2, C16.2, J1.3, J2.5, J2.6, U1.3 (D0), U1.4 (D1), U1.5 (D2), U1.6 (D3), U1.8 (GND), U2.3 (D0), U2.4 (D1), U2.5 (D2), U2.6 (D3), U2.8 (GND), U3.3 (D0), U3.4 (D1), U3.5 (D2), U3.6 (D3), U3.8 (GND), U4.14 (GND), U4.20 (~CS), U4.22 (~OE), U5.3 (D0), U5.4 (D1), U5.5 (D2), U5.6 (D3), U5.8 (GND), U6.1 (OE), U6.9 (D7), U6.10 (GND), U7.3 (D0), U7.4 (D1), U7.5 (D2), U7.6 (D3), U7.8 (GND), U8.1 (OE), U8.8 (D6), U8.9 (D7), U8.10 (GND), U9.1, U9.3 (GND), U10.1, U10.3 (GND), X1.4 (GND)
unnamed: J1.1, JP12.2 (C), TP1.1
unnamed: JP1.2 (C), JP3.3 (B)
unnamed: JP3.2 (C), TP3.1, U6.11 (Cp)
unnamed: JP11.2 (C), U8.11 (Cp)
unnamed: U1.10 (CET), U2.15 (TC)
unnamed: U2.10 (CET), U3.15 (TC)
unnamed: U3.10 (CET), U5.15 (TC)
unnamed: U4.11 (D0), U6.2 (D0)
unnamed: U4.12 (D1), U6.3 (D1)
unnamed: U4.13 (D2), U6.4 (D2)
unnamed: U4.15 (D3), U6.5 (D3)
unnamed: U4.16 (D4), U6.6 (D4)
unnamed: U4.17 (D5), U6.7 (D5)
unnamed: U4.18 (D6), U6.8 (D6)
unnamed: U9.2, U10.2, X1.5 (OUT)
VCC: C1.1, C2.1, C3.1, C4.1, C5.1, C6.1, C7.1, C8.1, C9.1, C10.2, C11.2, C12.1, C13.1, J1.7, J2.3, U1.7 (CEP), U1.9 (~PE), U1.16 (VCC), U2.7 (CEP), U2.9 (~PE), U2.16 (VCC), U3.7 (CEP), U3.9 (~PE), U3.16 (VCC), U4.27 (~WE), U4.28 (VCC), U5.7 (CEP), U5.9 (~PE), U5.10 (CET), U5.16 (VCC), U6.20 (VCC), U7.1 (~MR), U7.7 (CEP), U7.9 (~PE), U7.10 (CET), U7.16 (VCC), U8.20 (VCC), U9.5 (VCC), U10.5 (VCC), X1.1 (EN), X1.8 (Vcc)
